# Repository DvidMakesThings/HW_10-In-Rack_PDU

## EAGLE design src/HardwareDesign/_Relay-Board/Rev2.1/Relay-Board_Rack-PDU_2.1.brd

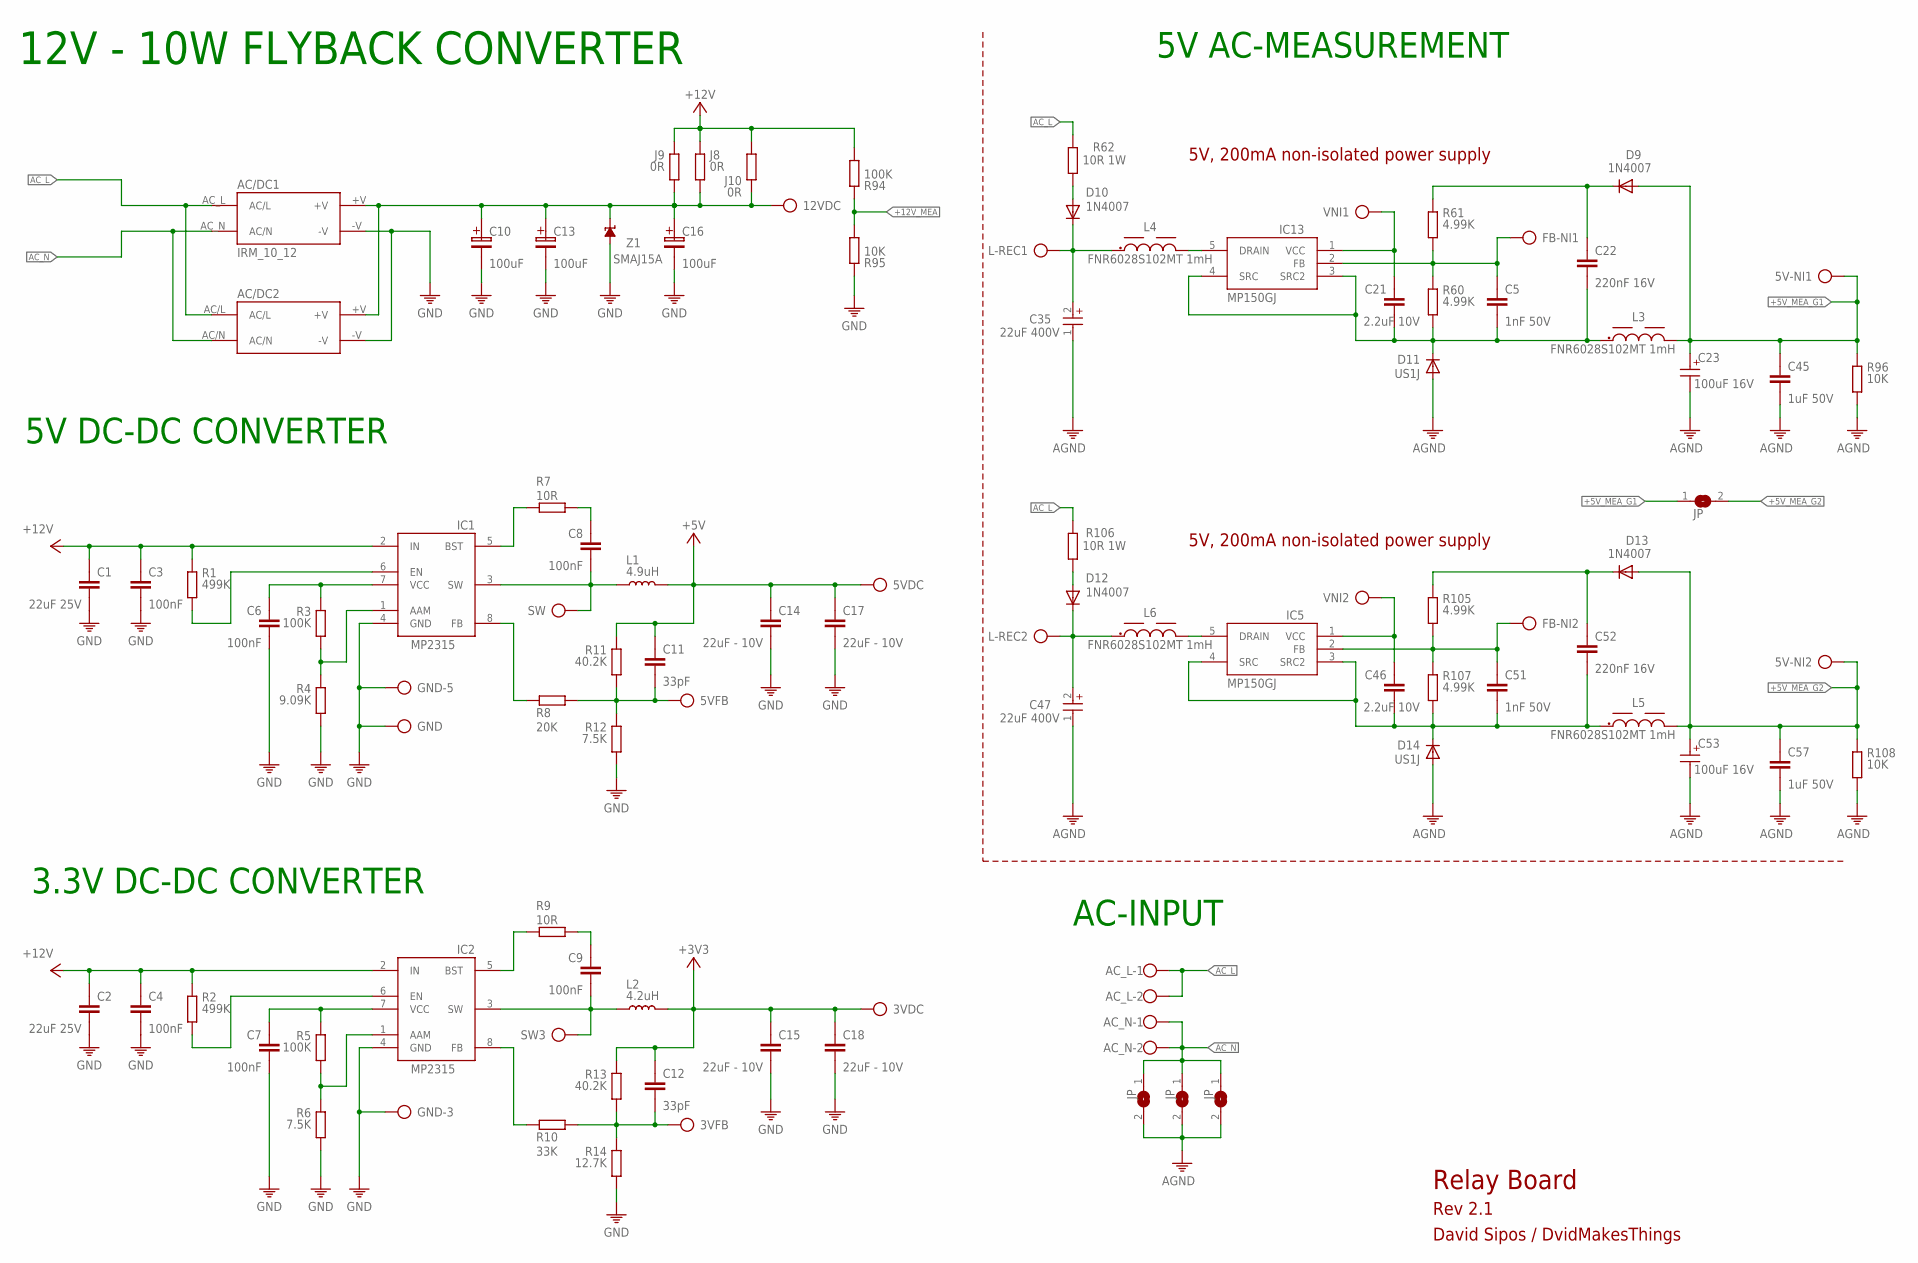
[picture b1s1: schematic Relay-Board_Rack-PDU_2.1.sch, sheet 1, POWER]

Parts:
3VDC, 3VFB, 5V-NI1, 5V-NI2, 5VDC, 5VFB, 12VDC: TP
AC/DC1: IRM_10_12
AC/DC2: IRM_10_12-2; IRM_15_12
AC_L: W237-102
AC_N: W237-102
C1, C2: 22uF 25V; C1206
C3, C4, C6, C7, C8, C9: 100nF; 0402
C5, C51: 1nF 50V; C0603
C10, C13, C16: 100uF; 100UF-16V
C11, C12: 33pF; 0402
C14, C15, C17, C18: 22uF - 10V; C1206
C21, C46: 2.2uF 10V; C0603
C22, C52: 220nF 16V; C0805
C23, C53: 100uF 16V; WCAP-PSHP_6.3X5.8(DXL)
C35, C47: 22uF 400V; WCAP-HSAH_D6.3H7.7P2.2
C45, C57: 1uF 50V; C0805
D9, D10, D12, D13: 1N4007; SMA
D11, D14: US1J; SMA
FB-NI1, FB-NI2: TP
GND: TP
GND-3, GND-5: TP
IC1: MP2315GJ-Z; SOT65P280X110-8N
IC2: MP2315S; SOT65P280X110-8N
IC5, IC13: MP150GJ; SOT23-5
J7: JP; SJ
J8, J9, J10: 0R; 0805
L1: 4.9uH; SRR5228A
L2: 4.2uH; SRR5228A
L3, L4, L5, L6: FNR6028S102MT 1mH; WE-HEPA_6030
L-REC1, L-REC2: TP
R1, R2: 499K; 0402
R3, R5, R94: 100K; 0402
R4: 9.09K; 0402
R6, R12: 7.5K; 0402
R7, R9: 10R; 0402
R8: 20K; 0402
R10: 33K; 0402
R11, R13: 40.2K; 0402
R14: 12.7K; 0402
R57, R58, R59: JP; SJ
R60, R61, R105, R107: 4.99K; 0603
R62, R106: 10R 1W; 2512
R95: 10K; 0402
R96, R108: 10K; 0805
SW, SW3: TP
VNI1, VNI2: TP
Z1: SMAJ15A; SUPRESSOR_SMAJ

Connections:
5VFB: 5VFB.TP, C11.2, R8.2, R11.2, R12.1
+3V3: 3VDC.TP, C12.1, C15.1, C18.1, L2.2, R13.1; also elsewhere on the board
+5V: 5VDC.TP, C11.1, C14.1, C17.1, L1.2, R11.1; also elsewhere on the board
+5V_MEA_G1: 5V-NI1.TP, C23.1 (+), C45.2, D9.A, J7.1, L3.2, R96.1; also elsewhere on the board
+5V_MEA_G2: 5V-NI2.TP, C53.1 (+), C57.2, D13.A, J7.2, L5.2, R108.1; also elsewhere on the board
+12V: C1.1, C2.1, C3.1, C4.1, IC1.2 (IN), IC2.2 (IN), J8.1, J9.1, J10.1, R1.1, R2.1, R94.2; also elsewhere on the board
+12V_MEA: R94.1, R95.2; also elsewhere on the board
AC_L: AC/DC1.AC_L (AC/L), AC/DC2.AC/L, AC_L.1, AC_L.2, R62.1, R106.1; also elsewhere on the board
AC_N: AC/DC1.AC_N (AC/N), AC/DC2.AC/N, AC_N.1, AC_N.2, R57.1, R58.1, R59.1
AGND: C23.2 (-), C35.1 (-), C45.1, C47.1 (-), C53.2 (-), C57.1, D11.A, D14.A, R57.2, R58.2, R59.2, R96.2, R108.2; also elsewhere on the board
GND: AC/DC1.-V, AC/DC2.-V, C1.2, C2.2, C3.2, C4.2, C6.2, C7.2, C10.2, C13.2, C14.2, C15.2, C16.2, C17.2, C18.2, GND.TP, GND-3.TP, GND-5.TP, IC1.4 (GND), IC2.4 (GND), R4.2, R6.2, R12.2, R14.2, R95.1, Z1.A; also elsewhere on the board
unnamed: 12VDC.TP, AC/DC1.+V, AC/DC2.+V, C10.1, C13.1, C16.1, J8.2, J9.2, J10.2, Z1.C
unnamed: D10.A, R62.2
unnamed: IC1.5 (BST), R7.2
unnamed: IC1.8 (FB), R8.1
unnamed: C8.1, R7.1
unnamed: IC1.6 (EN), R1.2
unnamed: C35.2 (+), D10.C, L4.1, L-REC1.TP
unnamed: C6.1, IC1.7 (VCC), R3.1
unnamed: C5.1, C21.1, C22.1, D11.C, IC13.3 (SRC2), IC13.4 (SRC), L3.1, R60.2
unnamed: C21.2, IC13.1 (VCC), VNI1.TP
unnamed: IC2.5 (BST), R9.2
unnamed: IC2.8 (FB), R10.1
unnamed: C9.1, R9.1
unnamed: 3VFB.TP, C12.2, R10.2, R13.2, R14.1
unnamed: IC2.6 (EN), R2.2
unnamed: C7.1, IC2.7 (VCC), R5.1
unnamed: IC1.1 (AAM), R3.2, R4.1
unnamed: IC2.1 (AAM), R5.2, R6.1
unnamed: C5.2, FB-NI1.TP, IC13.2 (FB), R60.1, R61.2
unnamed: D12.A, R106.2
unnamed: C22.2, D9.C, R61.1
unnamed: IC13.5 (DRAIN), L4.2
unnamed: C47.2 (+), D12.C, L6.1, L-REC2.TP
unnamed: C46.1, C51.1, C52.1, D14.C, IC5.3 (SRC2), IC5.4 (SRC), L5.1, R107.2
unnamed: C46.2, IC5.1 (VCC), VNI2.TP
unnamed: C51.2, FB-NI2.TP, IC5.2 (FB), R105.2, R107.1
unnamed: C52.2, D13.C, R105.1
unnamed: IC5.5 (DRAIN), L6.2
SW3: C9.2, IC2.3 (SW), L2.1, SW3.TP
SW5: C8.2, IC1.3 (SW), L1.1, SW.TP

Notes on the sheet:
12V - 10W FLYBACK CONVERTER
Relay Board
Rev 2.1
David Sipos / DvidMakesThings
5V DC-DC CONVERTER
3.3V DC-DC CONVERTER
5V AC-MEASUREMENT
AC-INPUT
5V, 200mA non-isolated power supply

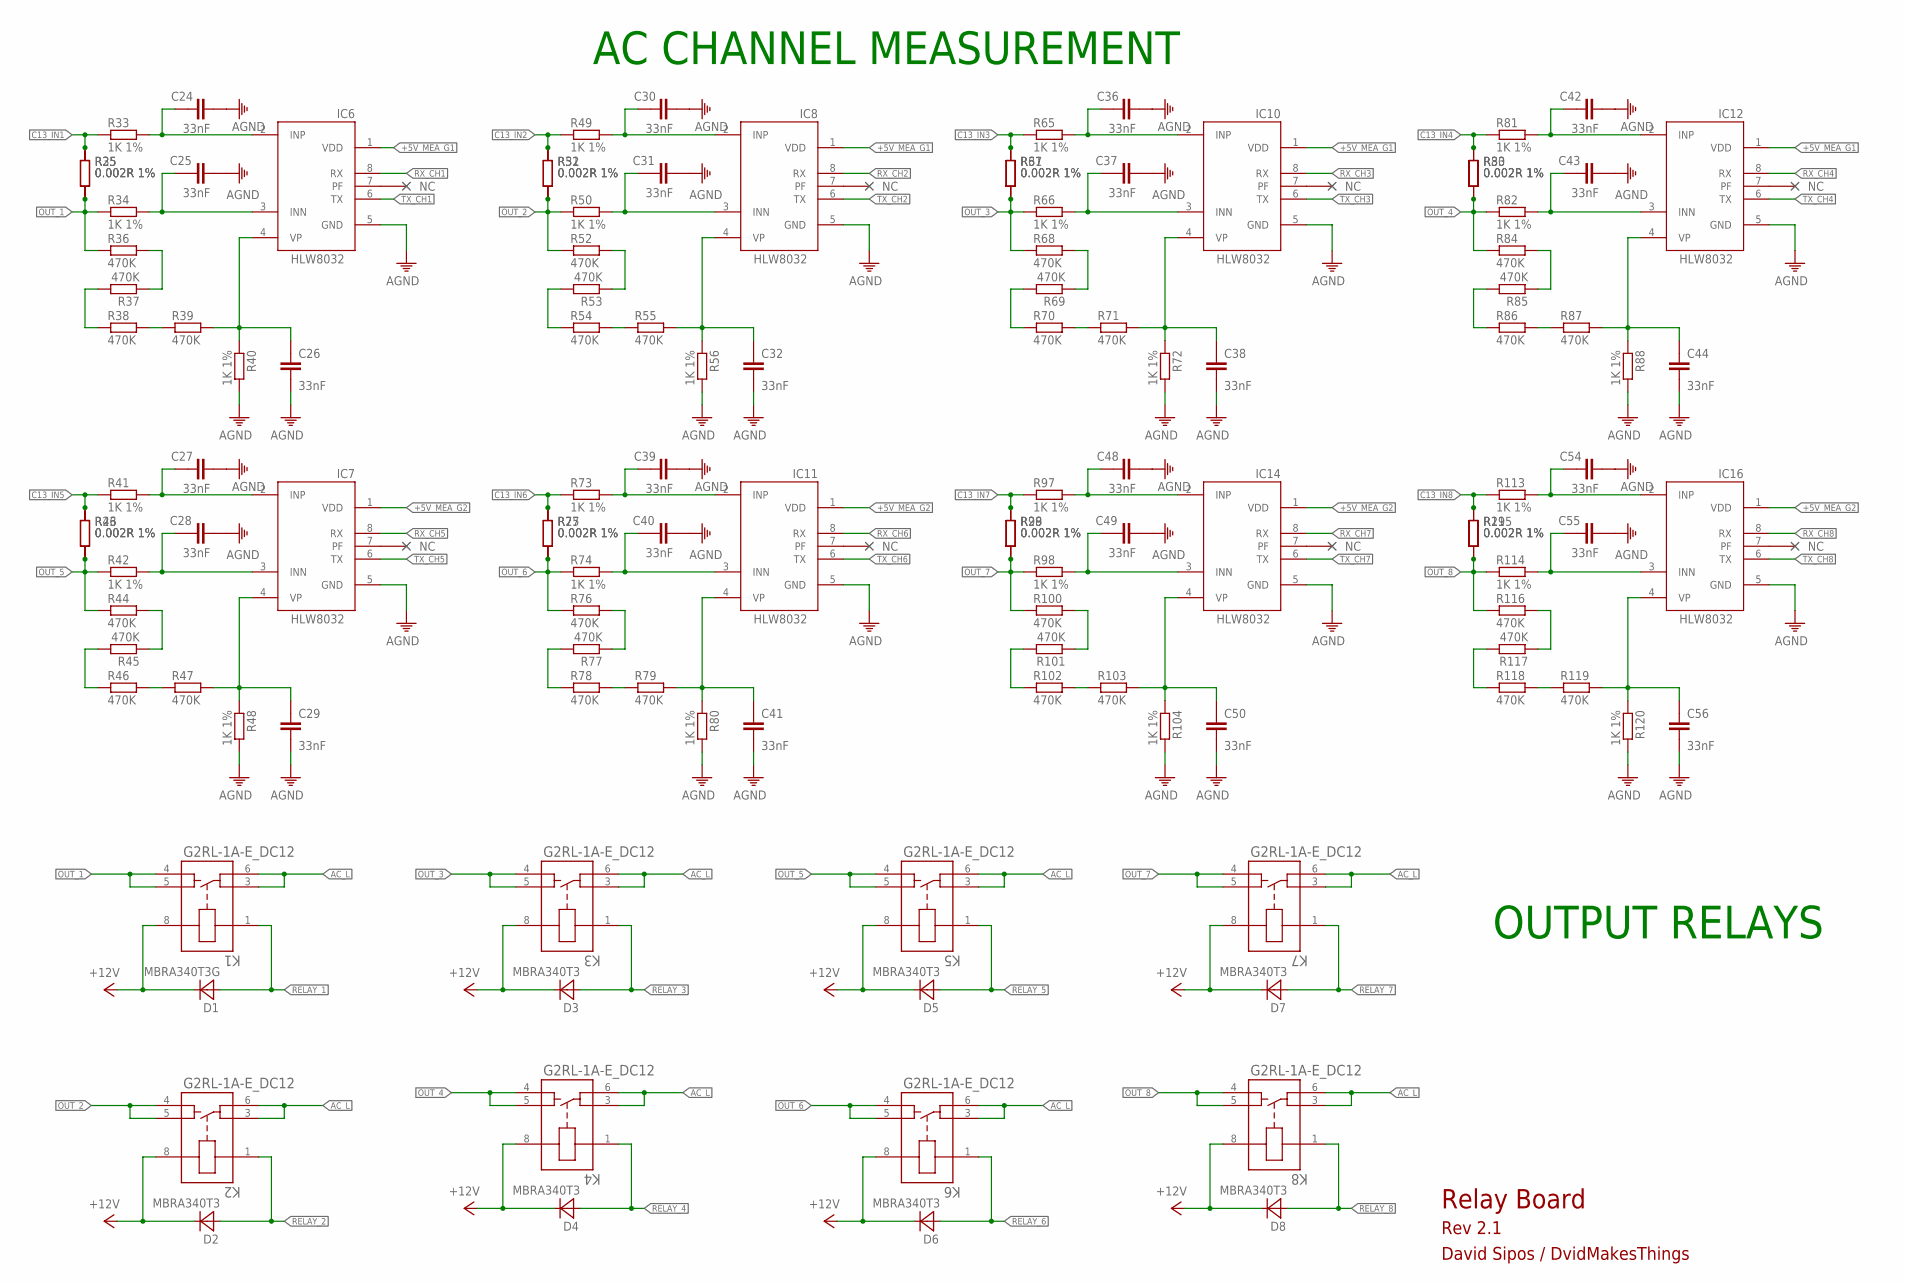
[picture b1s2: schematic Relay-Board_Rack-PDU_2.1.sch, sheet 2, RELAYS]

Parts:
C24, C25, C26, C27, C28, C29, C30, C31, C32, C36, C37, C38, C39, C40, C41, C42, C43, C44, C48, C49, C50, C54, C55, C56: 33nF; C1206
D1: MBRA340T3G; SMA
D2, D3, D4, D5, D6, D7, D8: MBRA340T3; SMA
IC6, IC7, IC8, IC10, IC11, IC12, IC14, IC16: HLW8032; SO8
K1, K2, K3, K4, K5, K6, K7, K8: G2RL-1A-E_DC12; RELAY_G2RL-1A-E_DC5_OMR
R25, R26, R27, R28, R29, R30, R31, R32, R35, R43, R51, R67, R75, R83, R99, R115: 0.002R 1%; 2512
R33, R34, R40, R41, R42, R48, R49, R50, R56, R65, R66, R72, R73, R74, R80, R81, R82, R88, R97, R98, R104, R113, R114, R120: 1K 1%; 1206
R36, R37, R38, R39, R44, R45, R46, R47, R52, R53, R54, R55, R68, R69, R70, R71, R76, R77, R78, R79, R84, R85, R86, R87, R100, R101, R102, R103, R116, R117, R118, R119: 470K; 1206

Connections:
+5V_MEA_G1: IC6.1 (VDD), IC8.1 (VDD), IC10.1 (VDD), IC12.1 (VDD); also elsewhere on the board
+5V_MEA_G2: IC7.1 (VDD), IC11.1 (VDD), IC14.1 (VDD), IC16.1 (VDD); also elsewhere on the board
+12V: D1.C, D2.C, D3.C, D4.C, D5.C, D6.C, D7.C, D8.C, K1.8, K2.8, K3.8, K4.8, K5.8, K6.8, K7.8, K8.8; also elsewhere on the board
AC_L: K1.3, K1.6, K2.3, K2.6, K3.3, K3.6, K4.3, K4.6, K5.3, K5.6, K6.3, K6.6, K7.3, K7.6, K8.3, K8.6; also elsewhere on the board
AGND: C24.2, C25.2, C26.2, C27.2, C28.2, C29.2, C30.2, C31.2, C32.2, C36.2, C37.2, C38.2, C39.2, C40.2, C41.2, C42.2, C43.2, C44.2, C48.2, C49.2, C50.2, C54.2, C55.2, C56.2, IC6.5 (GND), IC7.5 (GND), IC8.5 (GND), IC10.5 (GND), IC11.5 (GND), IC12.5 (GND), IC14.5 (GND), IC16.5 (GND), R40.2, R48.2, R56.2, R72.2, R80.2, R88.2, R104.2, R120.2; also elsewhere on the board
C13_IN1: R25.2, R33.1, R35.2
C13_IN2: R32.2, R49.1, R51.2
C13_IN3: R31.2, R65.1, R67.2
C13_IN4: R30.2, R81.1, R83.2
C13_IN5: R26.2, R41.1, R43.2
C13_IN6: R27.2, R73.1, R75.2
C13_IN7: R28.2, R97.1, R99.2
C13_IN8: R29.2, R113.1, R115.2
unnamed: C24.1, IC6.2 (INP), R33.2
unnamed: C25.1, IC6.3 (INN), R34.2
unnamed: R36.2, R37.1
unnamed: R37.2, R38.1
unnamed: R38.2, R39.1
unnamed: C26.1, IC6.4 (VP), R39.2, R40.1
unnamed: C27.1, IC7.2 (INP), R41.2
unnamed: C28.1, IC7.3 (INN), R42.2
unnamed: R44.2, R45.1
unnamed: R45.2, R46.1
unnamed: R46.2, R47.1
unnamed: C29.1, IC7.4 (VP), R47.2, R48.1
unnamed: C30.1, IC8.2 (INP), R49.2
unnamed: C31.1, IC8.3 (INN), R50.2
unnamed: R52.2, R53.1
unnamed: R53.2, R54.1
unnamed: R54.2, R55.1
unnamed: C32.1, IC8.4 (VP), R55.2, R56.1
unnamed: C36.1, IC10.2 (INP), R65.2
unnamed: C37.1, IC10.3 (INN), R66.2
unnamed: R68.2, R69.1
unnamed: R69.2, R70.1
unnamed: R70.2, R71.1
unnamed: C38.1, IC10.4 (VP), R71.2, R72.1
unnamed: C39.1, IC11.2 (INP), R73.2
unnamed: C40.1, IC11.3 (INN), R74.2
unnamed: R76.2, R77.1
unnamed: R77.2, R78.1
unnamed: R78.2, R79.1
unnamed: C41.1, IC11.4 (VP), R79.2, R80.1
unnamed: C42.1, IC12.2 (INP), R81.2
unnamed: C43.1, IC12.3 (INN), R82.2
unnamed: R84.2, R85.1
unnamed: R85.2, R86.1
unnamed: R86.2, R87.1
unnamed: C44.1, IC12.4 (VP), R87.2, R88.1
unnamed: C48.1, IC14.2 (INP), R97.2
unnamed: C49.1, IC14.3 (INN), R98.2
unnamed: R100.2, R101.1
unnamed: R101.2, R102.1
unnamed: R102.2, R103.1
unnamed: C50.1, IC14.4 (VP), R103.2, R104.1
unnamed: C54.1, IC16.2 (INP), R113.2
unnamed: C55.1, IC16.3 (INN), R114.2
unnamed: R116.2, R117.1
unnamed: R117.2, R118.1
unnamed: R118.2, R119.1
unnamed: C56.1, IC16.4 (VP), R119.2, R120.1
OUT_1: K1.4, K1.5, R25.1, R34.1, R35.1, R36.1
OUT_2: K2.4, K2.5, R32.1, R50.1, R51.1, R52.1
OUT_3: K3.4, K3.5, R31.1, R66.1, R67.1, R68.1
OUT_4: K4.4, K4.5, R30.1, R82.1, R83.1, R84.1
OUT_5: K5.4, K5.5, R26.1, R42.1, R43.1, R44.1
OUT_6: K6.4, K6.5, R27.1, R74.1, R75.1, R76.1
OUT_7: K7.4, K7.5, R28.1, R98.1, R99.1, R100.1
OUT_8: K8.4, K8.5, R29.1, R114.1, R115.1, R116.1
RELAY_1: D1.A, K1.1; also elsewhere on the board
RELAY_2: D2.A, K2.1; also elsewhere on the board
RELAY_3: D3.A, K3.1; also elsewhere on the board
RELAY_4: D4.A, K4.1; also elsewhere on the board
RELAY_5: D5.A, K5.1; also elsewhere on the board
RELAY_6: D6.A, K6.1; also elsewhere on the board
RELAY_7: D7.A, K7.1; also elsewhere on the board
RELAY_8: D8.A, K8.1; also elsewhere on the board
RX_CH1: IC6.8 (RX)
RX_CH2: IC8.8 (RX)
RX_CH3: IC10.8 (RX)
RX_CH4: IC12.8 (RX)
RX_CH5: IC7.8 (RX)
RX_CH6: IC11.8 (RX)
RX_CH7: IC14.8 (RX)
RX_CH8: IC16.8 (RX)
TX_CH1: IC6.6 (TX); also elsewhere on the board
TX_CH2: IC8.6 (TX); also elsewhere on the board
TX_CH3: IC10.6 (TX); also elsewhere on the board
TX_CH4: IC12.6 (TX); also elsewhere on the board
TX_CH5: IC7.6 (TX); also elsewhere on the board
TX_CH6: IC11.6 (TX); also elsewhere on the board
TX_CH7: IC14.6 (TX); also elsewhere on the board
TX_CH8: IC16.6 (TX); also elsewhere on the board

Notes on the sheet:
OUTPUT RELAYS
Relay Board
Rev 2.1
David Sipos / DvidMakesThings
AC CHANNEL MEASUREMENT

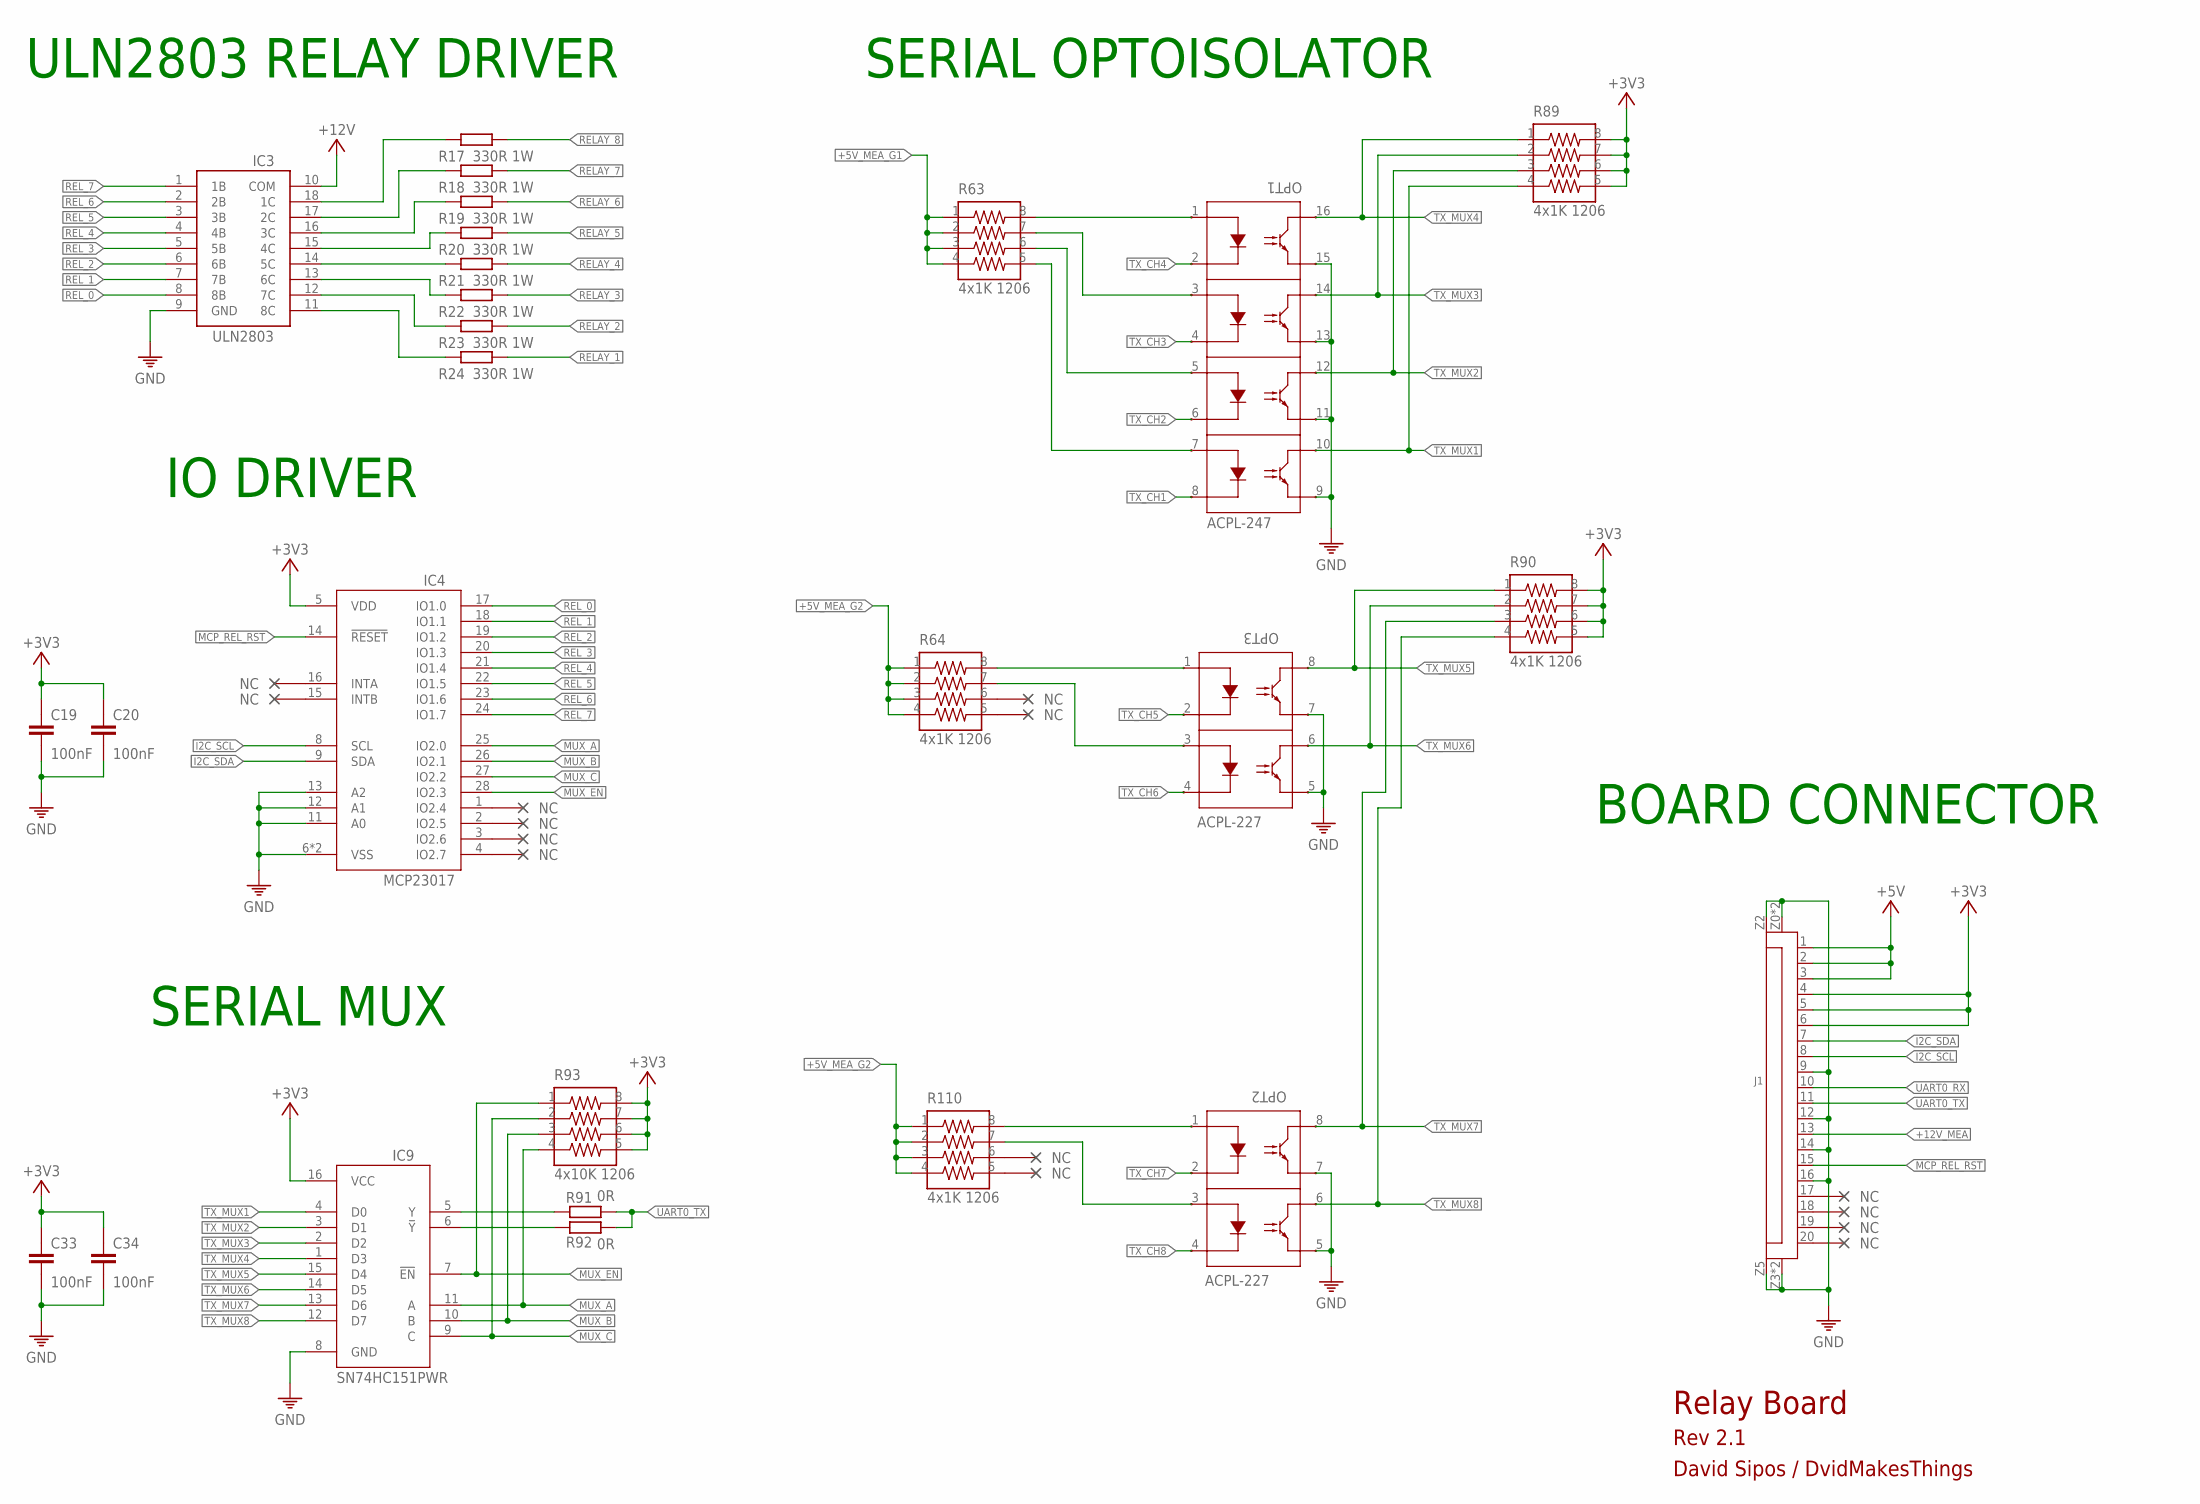
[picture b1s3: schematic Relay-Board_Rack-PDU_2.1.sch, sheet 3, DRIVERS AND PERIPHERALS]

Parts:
C19, C20, C33, C34: 100nF; C0402
IC3: ULN2803A; SO18
IC4: MCP23017-E/ML; QFN28[6X6]ML
IC9: SN74HC151PWR; TSSOP16
J1: FPC20-H; FPC20
OPT1: ACPL-247; SO16
OPT2, OPT3: ACPL-227; SO8
R17, R18, R19, R20, R21, R22, R23, R24: 330R 1W; 2512
R63, R64, R89, R90, R110: 4x1K 1206; 742C083103JP
R91, R92: 0R; 0402
R93: 4x10K 1206; 742C083103JP

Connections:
+3V3: C19.1, C20.1, C33.1, C34.1, IC4.5 (VDD), IC9.16 (VCC), J1.4, J1.5, J1.6, R89.5, R89.6, R89.7, R89.8, R90.5, R90.6, R90.7, R90.8, R93.5, R93.6, R93.7, R93.8; also elsewhere on the board
+5V: J1.1, J1.2, J1.3; also elsewhere on the board
+5V_MEA_G1: R63.1, R63.2, R63.3, R63.4; also elsewhere on the board
+5V_MEA_G2: R64.1, R64.2, R64.3, R64.4, R110.1, R110.2, R110.3, R110.4; also elsewhere on the board
+12V: IC3.10 (COM); also elsewhere on the board
+12V_MEA: J1.13; also elsewhere on the board
GND: C19.2, C20.2, C33.2, C34.2, IC3.9 (GND), IC4.6 (VSS), IC4.11 (A0), IC4.12 (A1), IC4.13 (A2), IC4.PAD (VSS), IC9.8 (GND), J1.9, J1.12, J1.14, J1.16, J1.Z0 (Z1), J1.Z1, J1.Z2, J1.Z3, J1.Z4 (Z3), J1.Z5 (Z4), OPT1.9, OPT1.11, OPT1.13, OPT1.15, OPT2.5, OPT2.7, OPT3.5, OPT3.7; also elsewhere on the board
I2C_SCL: IC4.8 (SCL), J1.8
I2C_SDA: IC4.9 (SDA), J1.7
MCP_REL_RST: IC4.14 (!RESET), J1.15
MUX_A: IC4.25 (IO2.0), IC9.11 (A), R93.4
MUX_B: IC4.26 (IO2.1), IC9.10 (B), R93.3
MUX_C: IC4.27 (IO2.2), IC9.9 (C), R93.2
MUX_EN: IC4.28 (IO2.3), IC9.7 (!EN), R93.1
unnamed: IC9.5 (Y), R91.1
unnamed: IC3.14 (5C), R21.1
unnamed: OPT1.1, R63.8
unnamed: IC3.11 (8C), R24.1
unnamed: IC3.12 (7C), R23.1
unnamed: IC3.13 (6C), R22.1
unnamed: OPT1.3, R63.7
unnamed: IC3.15 (4C), R20.1
unnamed: IC3.16 (3C), R19.1
unnamed: IC3.17 (2C), R18.1
unnamed: IC3.18 (1C), R17.1
unnamed: OPT1.5, R63.6
unnamed: OPT1.7, R63.5
unnamed: IC9.6 (!Y), R92.1
unnamed: OPT3.1, R64.8
unnamed: OPT3.3, R64.7
unnamed: OPT2.1, R110.8
unnamed: OPT2.3, R110.7
RELAY_1: R24.2; also elsewhere on the board
RELAY_2: R23.2; also elsewhere on the board
RELAY_3: R22.2; also elsewhere on the board
RELAY_4: R21.2; also elsewhere on the board
RELAY_5: R20.2; also elsewhere on the board
RELAY_6: R19.2; also elsewhere on the board
RELAY_7: R18.2; also elsewhere on the board
RELAY_8: R17.2; also elsewhere on the board
REL_0: IC3.8 (8B), IC4.17 (IO1.0)
REL_1: IC3.7 (7B), IC4.18 (IO1.1)
REL_2: IC3.6 (6B), IC4.19 (IO1.2)
REL_3: IC3.5 (5B), IC4.20 (IO1.3)
REL_4: IC3.4 (4B), IC4.21 (IO1.4)
REL_5: IC3.3 (3B), IC4.22 (IO1.5)
REL_6: IC3.2 (2B), IC4.23 (IO1.6)
REL_7: IC3.1 (1B), IC4.24 (IO1.7)
TX_CH1: OPT1.8; also elsewhere on the board
TX_CH2: OPT1.6; also elsewhere on the board
TX_CH3: OPT1.4; also elsewhere on the board
TX_CH4: OPT1.2; also elsewhere on the board
TX_CH5: OPT3.2; also elsewhere on the board
TX_CH6: OPT3.4; also elsewhere on the board
TX_CH7: OPT2.2; also elsewhere on the board
TX_CH8: OPT2.4; also elsewhere on the board
TX_MUX1: IC9.4 (D0), OPT1.10, R89.4
TX_MUX2: IC9.3 (D1), OPT1.12, R89.3
TX_MUX3: IC9.2 (D2), OPT1.14, R89.2
TX_MUX4: IC9.1 (D3), OPT1.16, R89.1
TX_MUX5: IC9.15 (D4), OPT3.8, R90.1
TX_MUX6: IC9.14 (D5), OPT3.6, R90.2
TX_MUX7: IC9.13 (D6), OPT2.8, R90.3
TX_MUX8: IC9.12 (D7), OPT2.6, R90.4
UART0_RX: J1.10
UART0_TX: J1.11, R91.2, R92.2

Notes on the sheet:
Relay Board
Rev 2.1
David Sipos / DvidMakesThings
ULN2803 RELAY DRIVER
IO DRIVER
SERIAL MUX
SERIAL OPTOISOLATOR
BOARD CONNECTOR

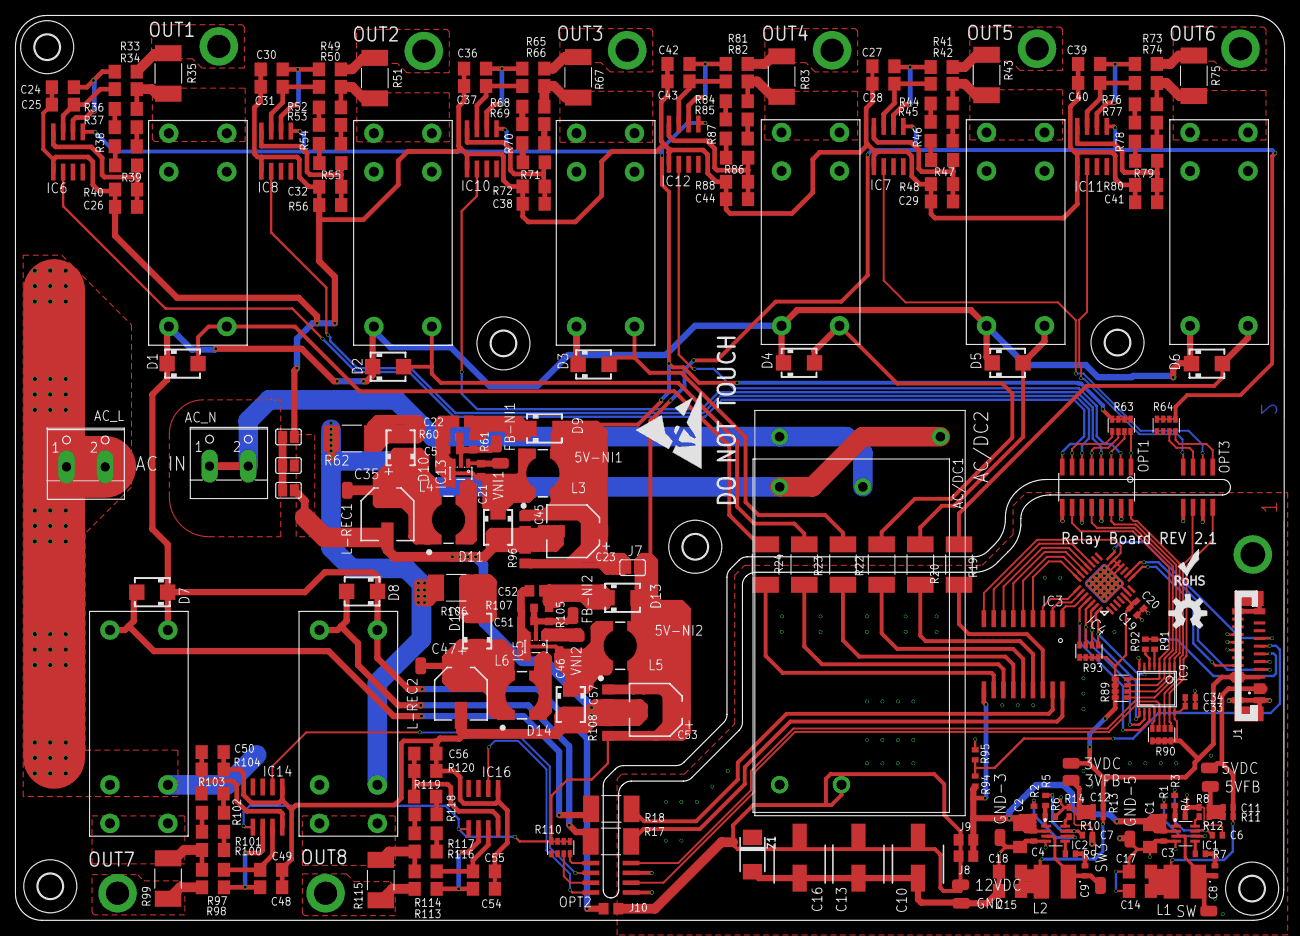
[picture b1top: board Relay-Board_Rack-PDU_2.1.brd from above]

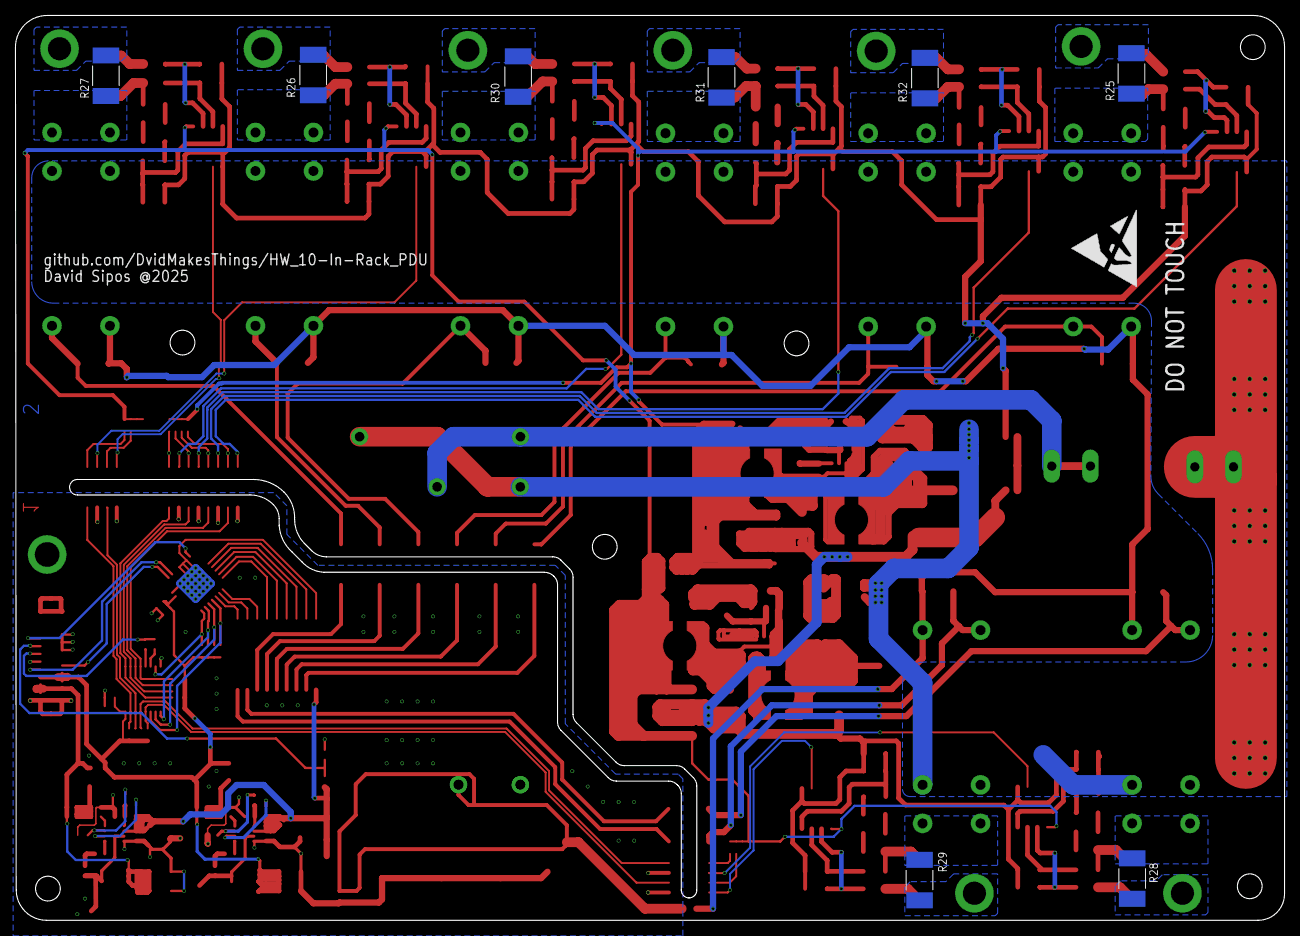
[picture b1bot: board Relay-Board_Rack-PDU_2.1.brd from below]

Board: 2 copper layers, 164.1 x 117.0 mm, 257 parts (9 on the bottom side), 163 nets.

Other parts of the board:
U$1, U$2: ESD_10.00
U$3: 2-LAYER
U$4, U$5, U$6, U$7, U$8, U$9: 3,2
U$10: OSHW-LOGO-M
U$11: ROHS_LOGO_0.18_IN

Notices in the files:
parts and their libraries:
ds_trafo: Copyright: Würth Elektronik
SparkFun-Aesthetics: Licensing: Creative Commons ShareAlike 4.0 International - https://creativecommons.org/licenses/by-sa/4.0
COPYRIGHT: Copyright (C) 2025 Ultra Librarian. All rights reserved.
